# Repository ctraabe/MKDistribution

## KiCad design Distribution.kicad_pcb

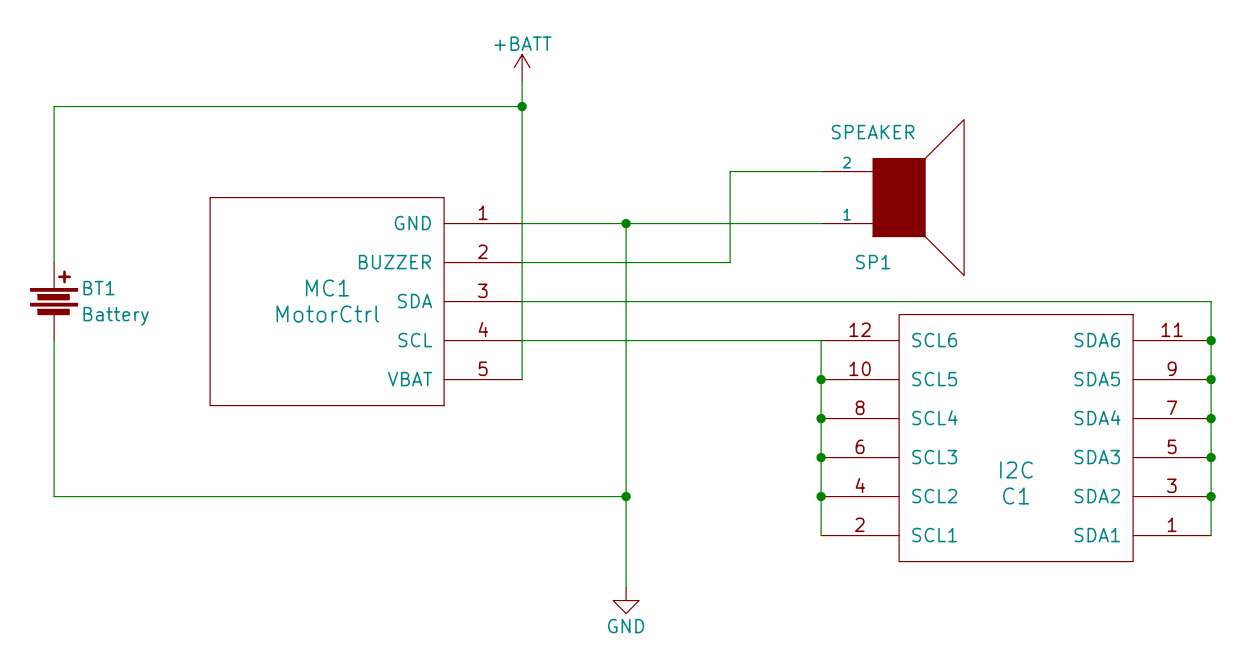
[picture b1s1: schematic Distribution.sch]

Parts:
BT1: Battery; Pin_Header_Straight_1x02
C1: I2C; Pin_Header_Straight_2x06
MC1: MotorCtrl; Molex_PicoBlade_53047-0510
SP1: SPEAKER; Pin_Header_Straight_1x02

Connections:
+BATT: BT1.1, MC1.5 (VBAT)
GND: BT1.2, MC1.1 (GND), SP1.1
unnamed: C1.1 (SDA1), C1.3 (SDA2), C1.5 (SDA3), C1.7 (SDA4), C1.9 (SDA5), C1.11 (SDA6), MC1.3 (SDA)
unnamed: C1.2 (SCL1), C1.4 (SCL2), C1.6 (SCL3), C1.8 (SCL4), C1.10 (SCL5), C1.12 (SCL6), MC1.4 (SCL)
unnamed: MC1.2 (BUZZER), SP1.2

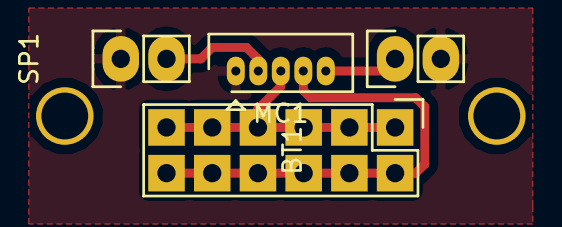
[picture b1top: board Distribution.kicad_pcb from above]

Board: 2 copper layers, 4 parts (0 on the bottom side), 5 nets.

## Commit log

2017-10-29 Added negative for top layer etching
2017-10-29 Updated for 2-layer board and added Elecrow files
